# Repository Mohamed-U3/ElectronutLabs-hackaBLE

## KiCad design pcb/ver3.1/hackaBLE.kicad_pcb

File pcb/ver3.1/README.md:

# U3 New developing board.
A compact Nordic nRF52832 BLE module for embedding in projects.
V3.1 is new board with deffrant size and CR2032 battery.

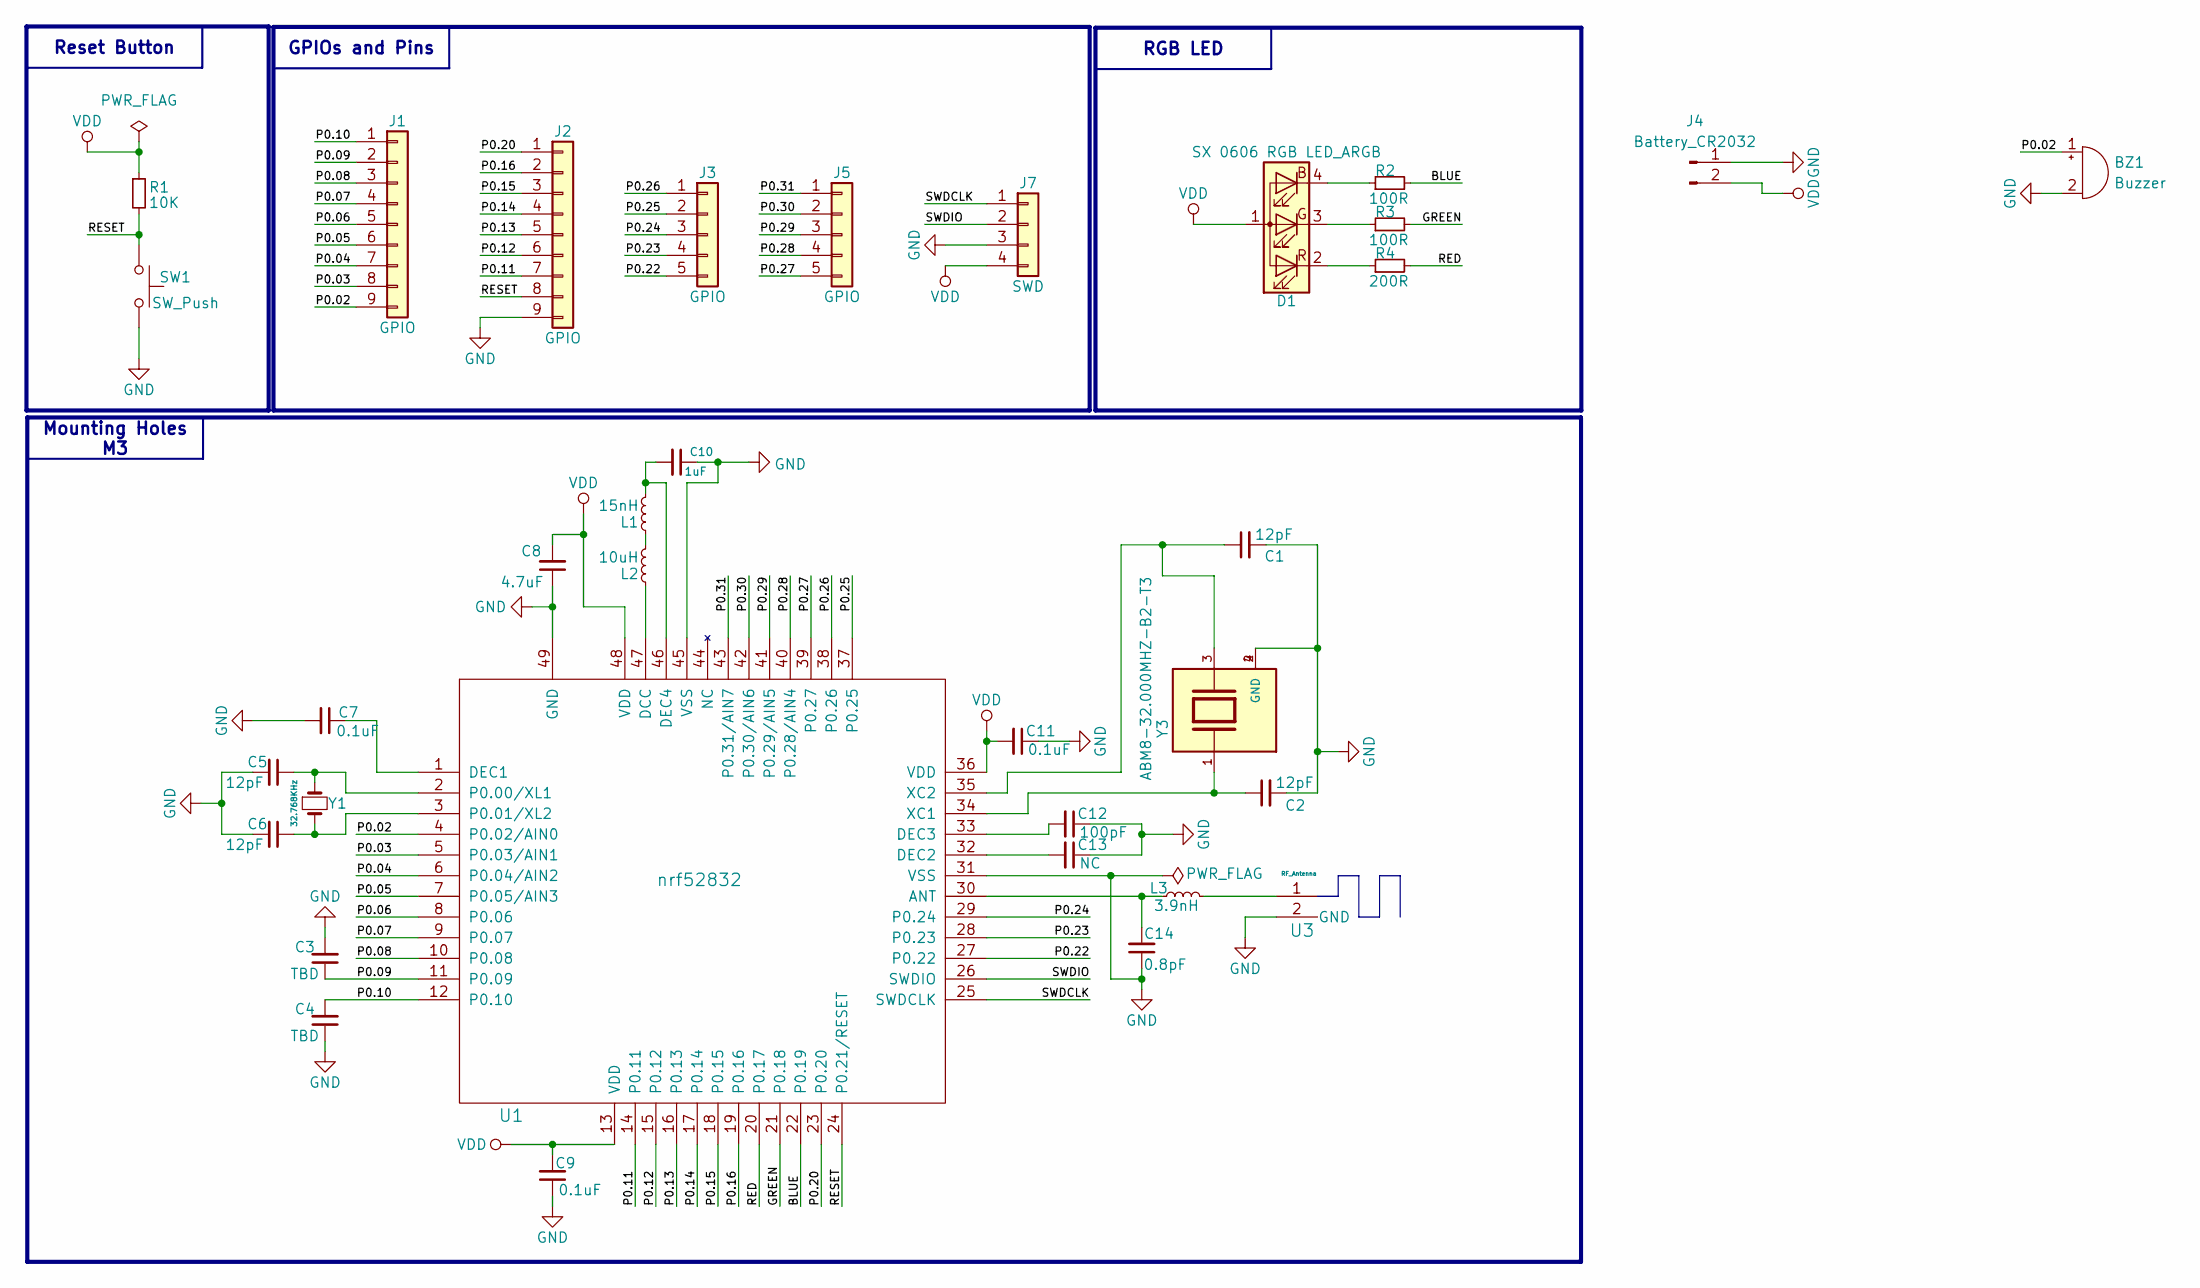
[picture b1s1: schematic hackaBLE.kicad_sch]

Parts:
BZ1: Buzzer; BUZ-SMD_L5.0-W5.5-P4.60
C1, C2, C5, C6: 12pF; C_0402_1005Metric_Pad0.74x0.62mm_HandSolder
C3, C4: TBD; C_0603_1608Metric_Pad1.08x0.95mm_HandSolder
C7, C9, C11: 0.1uF; C_0402_1005Metric_Pad0.74x0.62mm_HandSolder
C8: 4.7uF; C_0603_1608Metric_Pad1.08x0.95mm_HandSolder
C10: 1uF; C_0603_1608Metric_Pad1.08x0.95mm_HandSolder
C12: 100pF; C_0402_1005Metric_Pad0.74x0.62mm_HandSolder
C13: NC; C_0402_1005Metric_Pad0.74x0.62mm_HandSolder
C14: 0.8pF; C_0402_1005Metric_Pad0.74x0.62mm_HandSolder
D1: SX 0606 RGB LED_ARGB; RGB_LED
J1, J2: GPIO; PinHeaderStraight1x09_Pitch2.54mm
J3, J5: GPIO; 5pin_header
J4: Battery_CR2032; BatteryHolder_MYOUNG_BS-07-A1BJ001_CR2032
J7: SWD; Pin_Header_Straight_1x04_Pitch2.54
L1: 15nH; L_0402_1005Metric_Pad0.77x0.64mm_HandSolder
L2: 10uH; L_0603_1608Metric_Pad1.05x0.95mm_HandSolder
L3: 3.9nH; L_0402_1005Metric_Pad0.77x0.64mm_HandSolder
R1: 10K; R_0603_1608Metric_Pad0.98x0.95mm_HandSolder
R2, R3: 100R; R_0603_1608Metric_Pad0.98x0.95mm_HandSolder
R4: 200R; R_0603_1608Metric_Pad0.98x0.95mm_HandSolder
SW1: SW_Push; PTS810_Switch
U1: nrf52832; nRF52832
U3: RF_Antenna; Antenna-2.45GHZ_mirror
Y1: 32.768KHz; ABS07_crystal
Y3: ABM8-32.000MHZ-B2-T3; XTAL_ABM8-32.000MHZ-B2-T3; PARTREV 44041

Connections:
/BLUE: R2.2, U1.22 (P0.19)
/GREEN: R3.2, U1.21 (P0.18)
/P0.02: BZ1.1 (+), J1.9, U1.4 (P0.02/AIN0)
/P0.03: J1.8, U1.5 (P0.03/AIN1)
/P0.04: J1.7, U1.6 (P0.04/AIN2)
/P0.05: J1.6, U1.7 (P0.05/AIN3)
/P0.06: J1.5, U1.8 (P0.06)
/P0.07: J1.4, U1.9 (P0.07)
/P0.08: J1.3, U1.10 (P0.08)
/P0.09: C3.1, J1.2, U1.11 (P0.09)
/P0.10: C4.2, J1.1, U1.12 (P0.10)
/P0.11: J2.7, U1.14 (P0.11)
/P0.12: J2.6, U1.15 (P0.12)
/P0.13: J2.5, U1.16 (P0.13)
/P0.14: J2.4, U1.17 (P0.14)
/P0.15: J2.3, U1.18 (P0.15)
/P0.16: J2.2, U1.19 (P0.16)
/P0.20: J2.1, U1.23 (P0.20)
/P0.22: J3.5, U1.27 (P0.22)
/P0.23: J3.4, U1.28 (P0.23)
/P0.24: J3.3, U1.29 (P0.24)
/P0.25: J3.2, U1.37 (P0.25)
/P0.26: J3.1, U1.38 (P0.26)
/P0.27: J5.5, U1.39 (P0.27)
/P0.28: J5.4, U1.40 (P0.28/AIN4)
/P0.29: J5.3, U1.41 (P0.29/AIN5)
/P0.30: J5.2, U1.42 (P0.30/AIN6)
/P0.31: J5.1, U1.43 (P0.31/AIN7)
/RED: R4.2, U1.20 (P0.17)
/RESET: J2.8, R1.2, SW1.1, U1.24 (P0.21/RESET)
/SWDCLK: J7.1, U1.25 (SWDCLK)
/SWDIO: J7.2, U1.26 (SWDIO)
GND: BZ1.2 (-), C1.2, C2.2, C3.2, C4.1, C5.2, C6.2, C7.2, C8.1, C9.1, C10.1, C11.1, C12.1, C13.1, C14.1, J2.9, J4.1, J7.3, SW1.2, U1.31 (VSS), U1.45 (VSS), U1.49 (GND), U3.2 (GND), Y3.2 (GND), Y3.4 (GND)
unnamed: D1.4 (BK), R2.1
unnamed: D1.3 (GK), R3.1
unnamed: D1.2 (RK), R4.1
unnamed: L1.1, L2.2
unnamed: L3.2, U3.1
unnamed: C14.2, L3.1, U1.30 (ANT)
unnamed: L2.1, U1.47 (DCC)
unnamed: C7.1, U1.1 (DEC1)
unnamed: C13.2, U1.32 (DEC2)
unnamed: C12.2, U1.33 (DEC3)
unnamed: C10.2, L1.2, U1.46 (DEC4)
unnamed: C5.1, U1.2 (P0.00/XL1), Y1.1
unnamed: C6.1, U1.3 (P0.01/XL2), Y1.2
unnamed: C2.1, U1.34 (XC1), Y3.1
unnamed: C1.1, U1.35 (XC2), Y3.3
VDD: C8.2, C9.2, C11.2, D1.1 (A), J4.2, J7.4, R1.1, U1.13 (VDD), U1.36 (VDD), U1.48 (VDD)

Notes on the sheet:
RGB LED
GPIOs and Pins
Reset Button
Mounting Holes M3

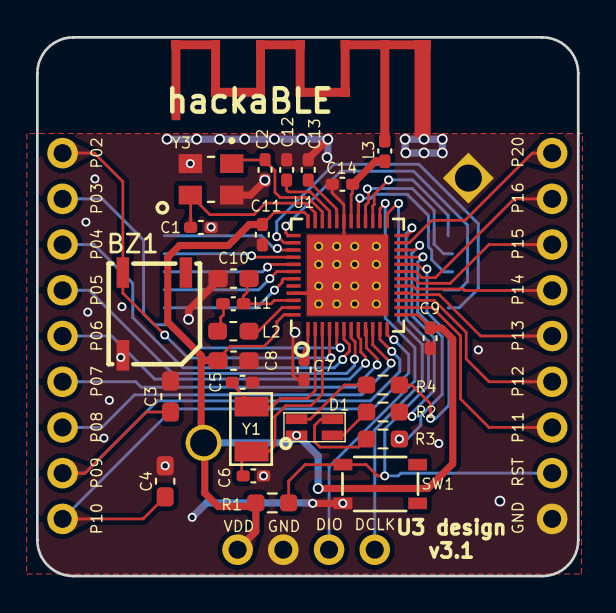
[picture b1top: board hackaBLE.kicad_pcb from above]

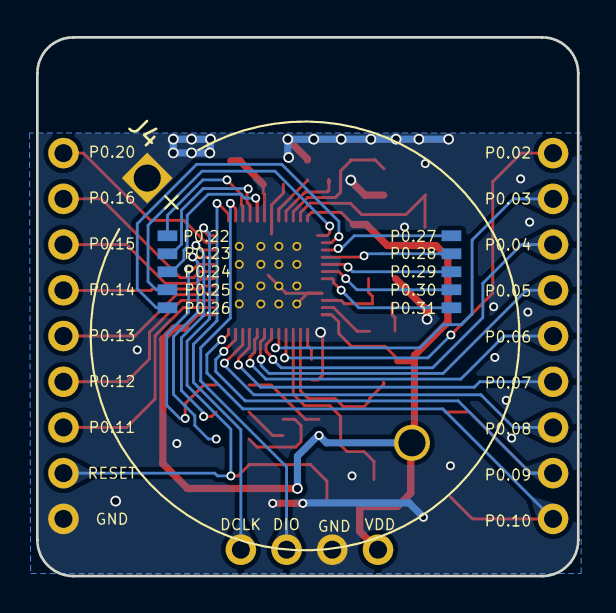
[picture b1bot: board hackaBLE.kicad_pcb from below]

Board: 2 copper layers, 30.1 x 29.9 mm, 34 parts (3 on the bottom side), 49 nets.

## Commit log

2025-08-05 New Version I made for me.. wait for the final edit.
2025-08-06 still working on it alot of error still there.
2025-08-06 now Version 3.0 has no Error and ready for manufacturing.
2025-08-06 adding readme file. will be edit later.
2025-08-09 feat: v3.1 adding CR2032 battery holder.
2025-08-09 all is left now is to get a place for the Buzzer in the schematics.
2025-08-09 I guess that is it.. I will manufacture this for testing.
2025-08-09 fix: small modifications for fabrication.
